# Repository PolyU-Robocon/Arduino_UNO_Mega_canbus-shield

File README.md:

# Arduino_UNO_Mega_canbus-shield
The USB can bus shield for arduino

# V2.1 release

## feature 

* SSD 1306 (i2C) support
* 1 x user led 
* 2x user button
* MPU9260 connector
* 24v DC input with step down
* MCP 2515 -> TJA1050 can bus support

## file support
KiCad 6.0 or above

## Test
not test yet

### Scheme
[embed]https://github.com/PolyU-Robocon/Arduino_UNO_Mega_canbus-shield/blob/dev/arduino_can_bus_shield_v2.1/_autosave-arduino_can_bus_shield_v2.1.pdf[/embed]

### 3D image
Front

Back

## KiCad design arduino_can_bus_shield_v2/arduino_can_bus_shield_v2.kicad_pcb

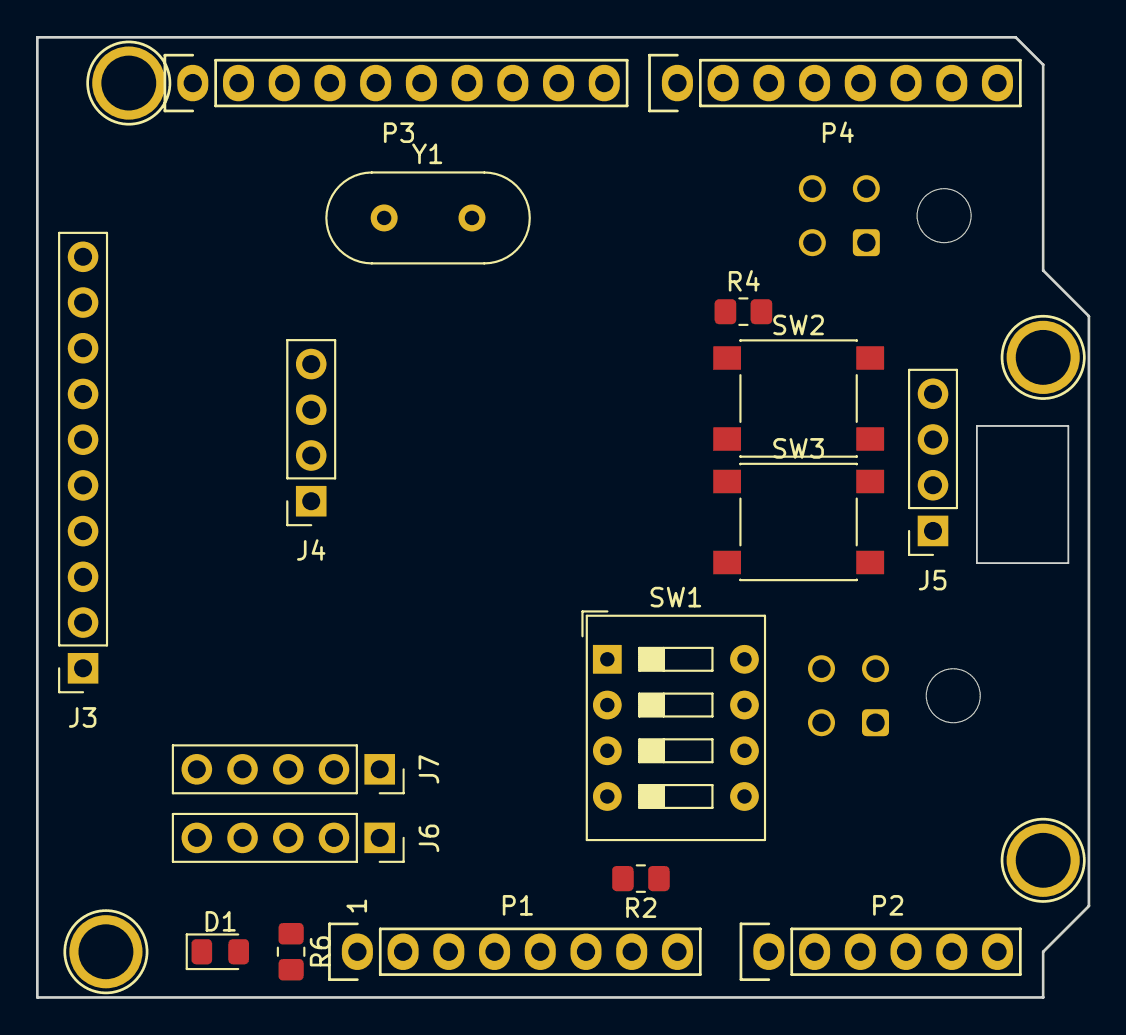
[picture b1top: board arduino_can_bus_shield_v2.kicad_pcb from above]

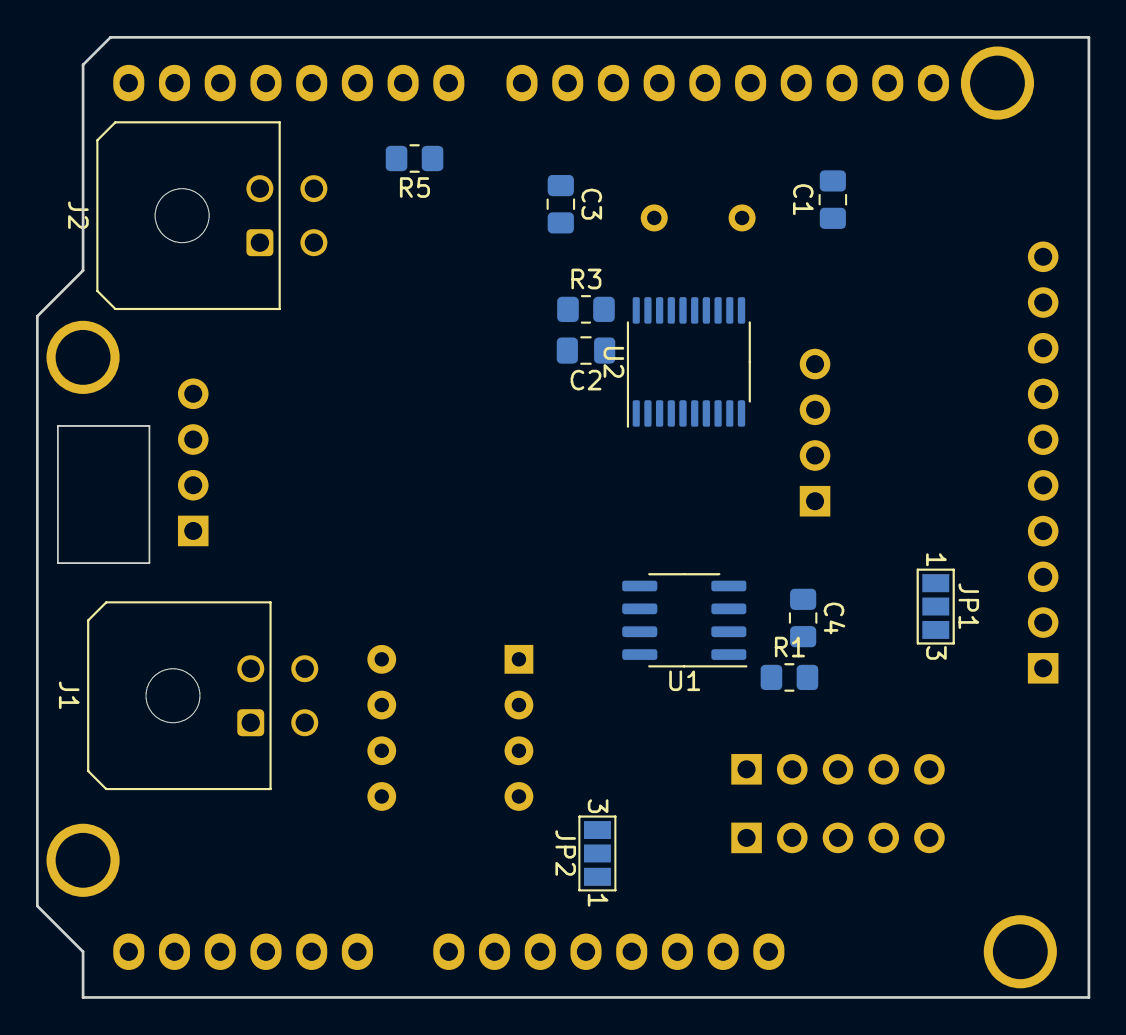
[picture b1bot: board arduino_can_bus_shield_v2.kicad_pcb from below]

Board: 2 copper layers, 58.4 x 53.3 mm, 34 parts (13 on the bottom side), 32 nets, no tracks yet.

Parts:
C1, C3: 22pF; C_0805_2012Metric_Pad1.18x1.45mm_HandSolder
C2, C4: 100nF; C_0805_2012Metric_Pad1.18x1.45mm_HandSolder
D1: power; LED_0805_2012Metric_Pad1.15x1.40mm_HandSolder
J1, J2: molex_3.0; Molex_Micro-Fit_3.0_43045-0400_2x02_P3.00mm_Horizontal
J3: MPU9250; PinSocket_1x10_P2.54mm_Vertical
J4: OLED; PinSocket_1x04_P2.54mm_Vertical
J5: UART2; PinSocket_1x04_P2.54mm_Vertical
J6: Encoder 1; PinSocket_1x05_P2.54mm_Vertical
J7: Encoder 0; PinSocket_1x05_P2.54mm_Vertical
JP1, JP2: Jumper; SolderJumper-3_P1.3mm_Open_Pad1.0x1.5mm_NumberLabels
P1: Power; Socket_Strip_Arduino_1x08
P2: Analog; Socket_Strip_Arduino_1x06
P3: Digital; Socket_Strip_Arduino_1x10
P4: Digital; Socket_Strip_Arduino_1x08
P5, P6, P7, P8: CONN_01X01; Arduino_1pin
R1: 17K; R_0805_2012Metric_Pad1.20x1.40mm_HandSolder
R2: 120; R_0805_2012Metric_Pad1.20x1.40mm_HandSolder
R3, R4, R5, R6: 10K; R_0805_2012Metric_Pad1.20x1.40mm_HandSolder
SW1: SW_DIP_x04; SW_DIP_SPSTx04_Slide_9.78x12.34mm_W7.62mm_P2.54mm
SW2, SW3: User; SW_Push_1P1T_NO_6x6mm_H9.5mm
U1: MCP2551-I-SN; SOIC-8_3.9x4.9mm_P1.27mm
U2: MCP2515-xST; TSSOP-20_4.4x6.5mm_P0.65mm
Y1: 16MHz; Crystal_HC49-U_Vertical

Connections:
+3V3: JP1.2 (C), JP2.2 (C), P1.4
+5V: J5.1, J6.1, J7.1, JP1.3 (B), JP2.3 (B), P1.5, R3.1, R6.1, SW1.1, SW2.2, SW3.2
/0(Rx): J5.2, P4.8
/1(Tx): J5.3, P4.7
/2: J6.2, P4.6
/3(**): J7.2, P4.5
/4: J6.3, P4.4
/5(**): J7.3, P4.3, R5.1, SW3.1
/6(**): P4.2, R4.1, SW2.1
/7: P4.1, U2.18 (~CS)
/12(MISO): P3.6, U2.17 (SO)
/13(SCK): P3.5, U2.14 (SCK)
/A0: J7.4, P2.1
/A1: J6.4, P2.2
/A4(SDA): J3.7, J4.4, P2.5, P3.2
/A5(SCL): J3.8, J4.3, P2.6, P3.1
/CAN+: J1.1, J2.1, R2.1, U1.7 (CANH)
/CAN-: J1.2, J2.2, SW1.5, U1.6 (CANL)
/CAN_Rx: U1.4 (RXD), U2.2 (RXCAN)
/CAN_Tx: U1.1 (TXD), U2.1 (TXCAN)
/can_enable: C2.1, C4.1, SW1.8, U1.3 (VDD), U2.20 (VDD)
GND: C1.2, C2.2, C3.2, C4.2, D1.1 (K), J3.9, J4.1, J5.4, J6.5, J7.5, P1.6, P1.7, P3.4, R1.2, R4.2, R5.2, SW1.6, SW1.7, U1.2 (VSS), U2.10 (VSS)
unnamed: C1.1, U2.8 (OSC2), Y1.1
unnamed: C3.1, U2.9 (OSC1), Y1.2
unnamed: D1.2 (A), R6.2
unnamed: J1.3, SW1.3
unnamed: J2.3, SW1.2
unnamed: J3.10, JP2.1 (A)
unnamed: J4.2, JP1.1 (A)
unnamed: R1.1, U1.8 (Rs)
unnamed: R2.2, SW1.4
unnamed: R3.2, U2.19 (~RESET)

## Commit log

2022-08-22 v2.1release
2022-08-22 v2.1 added BOM
2022-08-24 fixed pin 9 button to pin 6
